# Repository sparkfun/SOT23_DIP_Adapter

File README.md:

SOT23 DIP Adapter
=================

[
*SparkFun SOT23 to DIP Adapter(BOB-00717)*](https://www.sparkfun.com/products/717)

This pcb breaks out SOT23 packages to standard 0.1" headers for DIP packages. 

Repository Contents
-------------------
* **/Hardware** - All Eagle design files (.brd, .sch)

License Information
-------------------
The hardware is released under [Creative Commons ShareAlike 4.0 International](https://creativecommons.org/licenses/by-sa/4.0/).

Distributed as-is; no warranty is given.

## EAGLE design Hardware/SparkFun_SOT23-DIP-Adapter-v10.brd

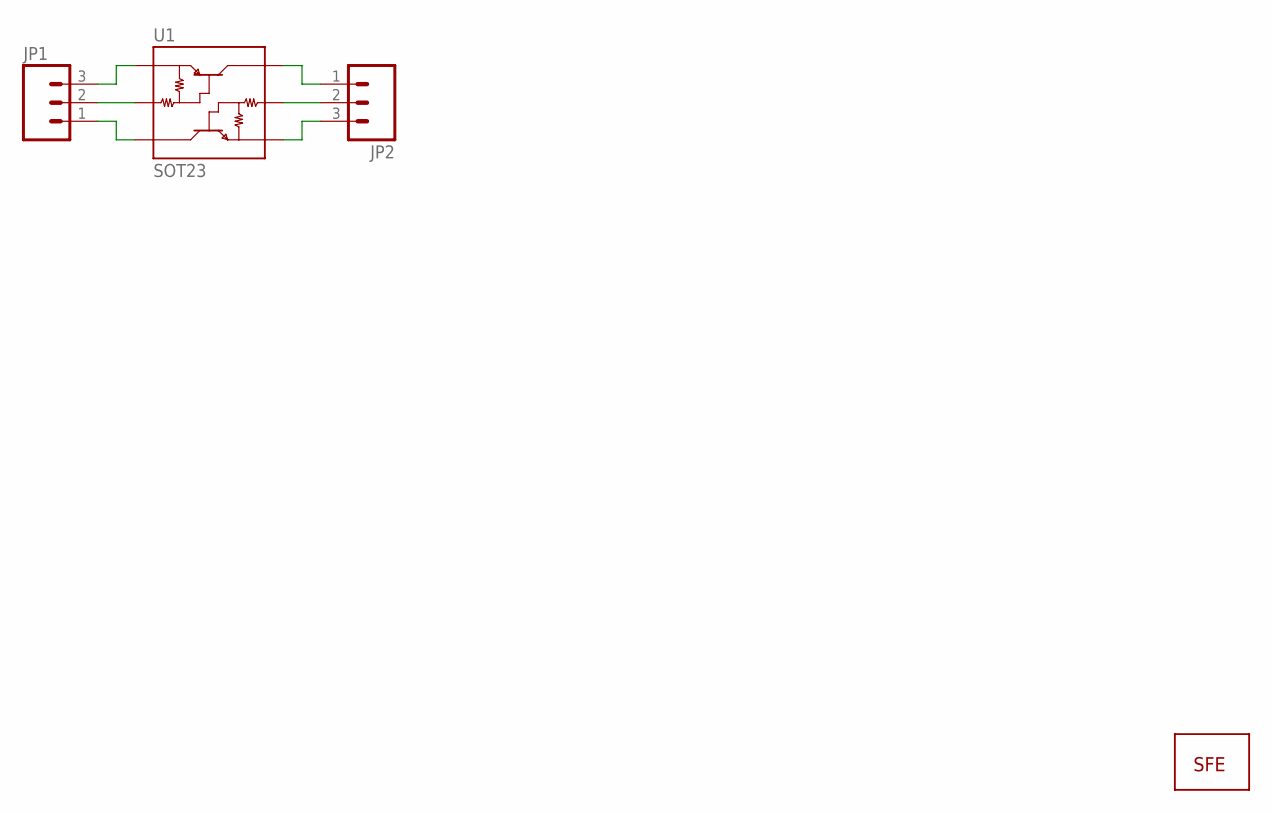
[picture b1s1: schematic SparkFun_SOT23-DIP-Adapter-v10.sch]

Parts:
JP1, JP2: M03PTH; 1X03
U1: SOT23; SOT23-6
U$1: LOGO-SFESK; SFE-LOGO-FLAME

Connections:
unnamed: JP2.1, U1.4 (C2)
unnamed: JP2.2, U1.5 (B1)
unnamed: JP2.3, U1.6 (E1)
unnamed: JP1.3, U1.3 (E2)
unnamed: JP1.2, U1.2 (B2)
unnamed: JP1.1, U1.1 (C1)

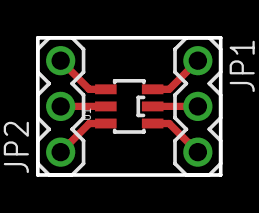
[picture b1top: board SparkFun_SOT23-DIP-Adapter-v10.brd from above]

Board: 2 copper layers, 10.2 x 7.6 mm, 4 parts (1 on the bottom side), 6 nets.

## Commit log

2015-01-06 Initial hardware commit
